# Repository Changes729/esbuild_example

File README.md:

# esbuild_example

## Chinese Users

``` sh
# install cnpm
npm install cnpm -g  --registry=https://registry.npm.taobao.org

cnpm install --save-dev @electron-forge/cli
cnpm exec --package=@electron-forge/cli -c "electron-forge import"
```

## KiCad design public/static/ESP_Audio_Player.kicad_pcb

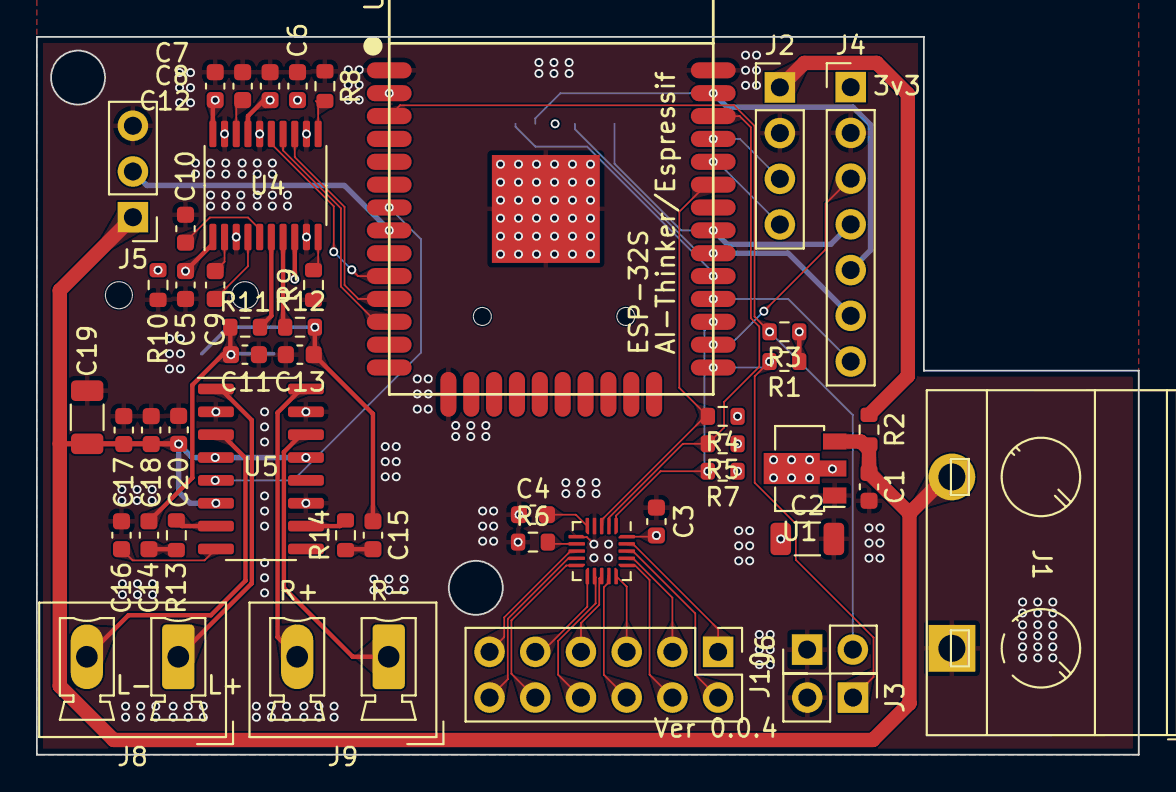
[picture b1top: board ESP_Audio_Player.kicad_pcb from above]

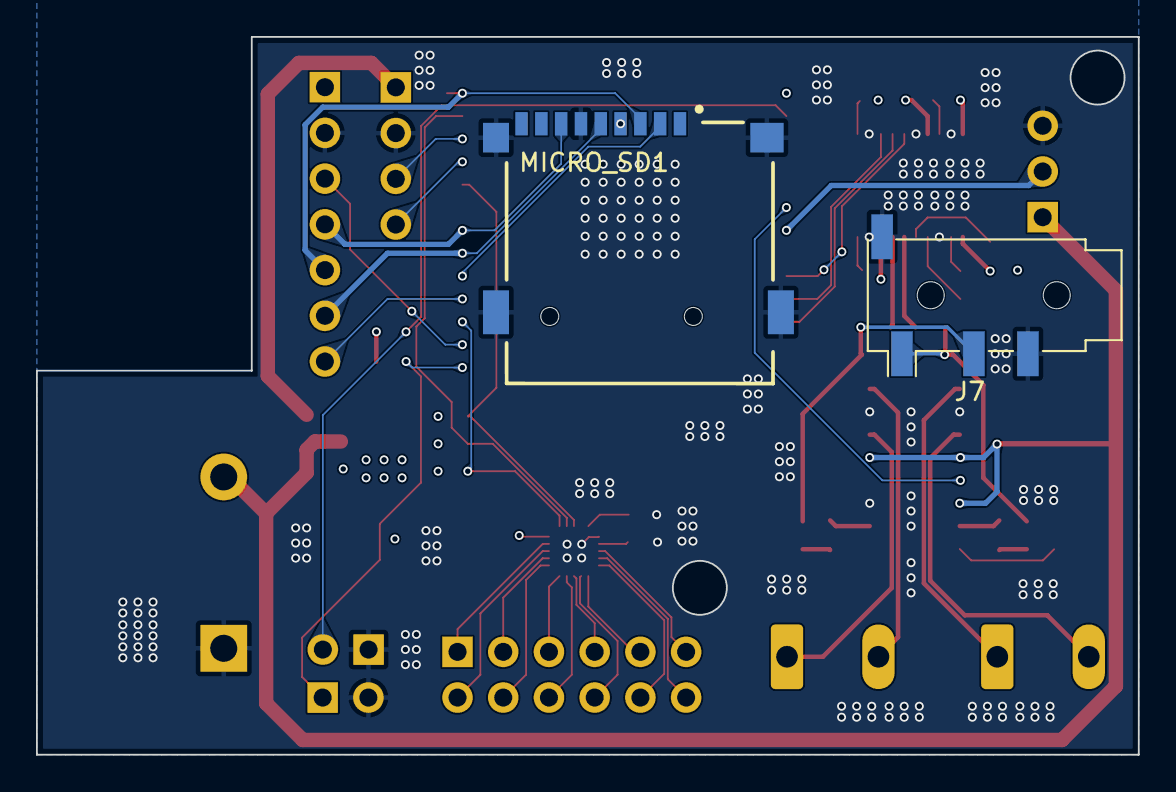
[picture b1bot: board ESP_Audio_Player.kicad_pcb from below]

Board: 4 copper layers, 61.2 x 39.9 mm, 50 parts (2 on the bottom side), 55 nets.

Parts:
C1, C8: 10uF; C_0603_1608Metric
C2: 10uF; C_1206_3216Metric
C3, C4, C5, C6, C7, C12, C14, C15, C16: 0.1uF; C_0603_1608Metric
C9, C10, C11, C13: 2.2uF; C_0603_1608Metric
C17, C18, C20: 1uF; C_0603_1608Metric
C19: 470uF; C_1206_3216Metric
J1: AC_IN; HB-9500
J2: UART_DOWNLOAD; PinHeader_1x04_P2.54mm_Vertical
J3: DMODE; PinHeader_1x02_P2.54mm_Vertical
J4: RC522_pins; PinHeader_1x07_P2.54mm_Vertical
J5: Conn_01x03; PinHeader_1x03_P2.54mm_Vertical
J6: Conn_01x02; PinHeader_1x02_P2.54mm_Vertical
J7: AudioJack4; Jack_3.5mm_PJ320D_Horizontal
J8, J9: Conn_01x02; PhoenixContact_MCV_1,5_2-G-5.08_1x02_P5.08mm_Vertical
J10: Conn_02x06_Odd_Even; PinHeader_2x06_P2.54mm_Vertical
MICRO_SD1: TF-01A
R1, R3: 12k; R_0603_1608Metric
R2: 0; R_0603_1608Metric
R4, R5, R7: 1k; R_0603_1608Metric
R6: 75k 1%; R_0603_1608Metric
R8, R9, R10: 100k; R_0603_1608Metric
R11, R12: 470; R_0603_1608Metric
R13, R14: 10k; R_0603_1608Metric
U1: AMS1117-3.3; SOT-89-3
U2: ESP-32S
U3: MPR121QR2; UQFN-20_3x3mm_P0.4mm
U4: PCM5102; TSSOP-20_4.4x6.5mm_P0.65mm
U5: PAM8403D; SOP-16_3.9x9.9mm_P1.27mm

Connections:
+3V3: C2.1, C3.1, C5.1, C6.1, C7.1, C8.1, J4.1, MICRO_SD1.4 (VDD), R1.1, R3.1, R4.1, R5.1, R7.1, R10.2, U1.2 (VO), U2.2 (3V3), U3.20 (VDD), U4.1 (CPVDD), U4.8 (AVDD), U4.17 (XSMT), U4.20 (DVDD)
+5V: C1.1, C17.2, C18.2, C19.2, C20.2, J1.2, J5.1, R2.2, U1.3 (VI), U5.4 (PVDD), U5.6 (VDD), U5.13 (PVDD)
/AUDIO_L: C11.2, C14.1, J7.T, R11.2
/AUDIO_MUTE: U2.7 (IO35), U5.5 (~MUTE)
/AUDIO_R: C13.2, C15.1, J7.R1, R12.2
/ESP_EN: J6.2, R3.2, U2.3 (EN)
/I2C_SCL: R5.2, U2.36 (IO22), U3.2 (SCL)
/I2C_SDA: R4.2, U2.33 (IO21), U3.3 (SDA)
/I2S_BCLK: U2.11 (IO26), U4.13 (BCK)
/I2S_DO: U2.12 (IO27), U4.14 (DIN)
/I2S_LRC: U2.10 (IO25), U4.15 (LRCK)
/IO0: J3.1, R1.2, U2.25 (IO0)
/MPR121/ELE0: J10.11, U3.8 (ELE0)
/MPR121/ELE1: J10.12, U3.9 (ELE1)
/MPR121/ELE2: J10.10, U3.10 (ELE2)
/MPR121/ELE3: J10.9, U3.11 (ELE3)
/MPR121/ELE4: J10.8, U3.12 (LED0/ELE4)
/MPR121/ELE5: J10.7, U3.13 (LED1/ELE5)
/MPR121/ELE6: J10.6, U3.14 (LED2/ELE6)
/MPR121/ELE7: J10.5, U3.15 (LED3/ELE7)
/MPR121/ELE8: J10.4, U3.16 (LED4/ELE8)
/MPR121/ELE9: J10.3, U3.17 (LED5/ELE9)
/MPR121/ELE10: J10.2, U3.18 (LED6/ELE10)
/MPR121/ELE11: J10.1, U3.19 (LED7/ELE11)
/PAM8403/+AOUT_L: J8.1, U5.1 (LOUT+)
/PAM8403/+AOUT_R: J9.2, U5.16 (ROUT+)
/PAM8403/-AOUT_L: J8.2, U5.3 (LOUT-)
/PAM8403/-AOUT_R: J9.1, U5.14 (ROUT-)
/PCM5102/DEMP_EN: R9.2, U4.10 (DEMP)
/PCM5102/FLT_EN: R8.2, U4.11 (FLT)
/RC522_SPI_CS: J4.7, U2.28 (IO17)
/RXD: J2.4, U2.34 (RXD0)
/SD_SPI_CS: MICRO_SD1.2 (CD/DAT3), U2.29 (IO5)
/TXD: J2.3, U2.35 (TXD0)
/VSPI_MISO: J4.4, MICRO_SD1.7 (DAT0), U2.31 (IO19)
/VSPI_MOSI: J4.5, MICRO_SD1.3 (CMD), U2.37 (IO23)
/VSPI_SCLK: J4.6, MICRO_SD1.5 (CLK), U2.30 (IO18)
/WS2812_SIG: J5.2, U2.8 (IO32)
/~IRQ: R7.2, U2.27 (IO16), U3.1 (~IRQ)
/~RC522_RST: J4.3, U2.26 (IO4)
GND: C1.2, C2.2, C3.2, C4.1, C5.2, C6.2, C7.2, C8.2, C10.1, C11.1, C12.1, C13.1, C16.1, C17.1, C18.1, C19.1, C20.1, J1.1, J2.2, J3.2, J4.2, J5.3, J6.1, J7.R2, J7.S, MICRO_SD1.6 (VSS), MICRO_SD1.MP1 (SHIELD), MICRO_SD1.MP2 (SHIELD), MICRO_SD1.MP3 (SHIELD), MICRO_SD1.MP4 (SHIELD), R6.1, R8.1, R9.1, R10.1, U1.1 (GND), U2.1 (GND), U2.15 (GND), U2.38 (GND), U2.39 (GND-PAD), U3.4 (ADDR), U3.6 (VSS), U4.3 (CPGND), U4.9 (AGND), U4.12 (SCK), U4.16 (FMT), U4.19 (DGND), U5.2 (PGND), U5.11 (GND), U5.15 (PGND)
unnamed: C14.2, R13.1
unnamed: C15.2, R14.1
unnamed: R6.2, U3.7 (REXT)
unnamed: C4.2, U3.5 (VREG)
unnamed: C9.1, U4.4 (CAPM)
unnamed: C9.2, U4.2 (CAPP)
unnamed: C12.2, U4.18 (LDOO)
unnamed: R11.1, U4.6 (OUTL)
unnamed: R12.1, U4.7 (OUTR)
unnamed: C10.2, U4.5 (VNEG)
unnamed: R13.2, U5.7 (INL)
unnamed: R14.2, U5.10 (INR)
unnamed: C16.2, U5.8 (VREF)
VDD: J2.1, R2.1

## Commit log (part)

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2024-02-23 [INTERNAL] 修改 esbuild 脚本，添加最小demo
2024-02-23 [INTERNAL] add electron support
2024-02-23 [INTERNAL] 修正
2024-03-01 添加 kicanvas 案例
2024-03-01 [INTERNAL] add pdf load example
2024-03-01 更新 html 版本和 react 动态版本的
2024-03-04 更新编译脚本。
2024-03-04 ThreeJS box example.
2024-03-22 添加 gltf example
2024-04-24 Wed Apr 24 10:22:11 CST 2024
2024-06-23 [NBF] test svg load in js, and operation with it.
2024-07-17 add excalidraw example.
2024-12-18 [INTERNAL] basic router usage.
2024-12-18 [INTERNAL] support router
2024-12-18 [INTERNAL] support scss.
2024-12-18 [INTERNAL] mass commit.
2024-12-18 [INTERNAL] merge some useless files into one react.
2024-12-19 Thu Dec 19 15:33:06 CST 2024
2024-12-21 [RELEASE] basic framework
2024-12-21 [INTERNAL] add milkdown example.
2025-01-29 marked example.
2025-01-29 update ipc call
2025-01-31 fix markdown load error. remove useless console output.
2025-02-02 test getPosition
2025-02-05 add test for web filesystem API.
2025-04-24 simple ts project
2025-04-24 add p5 example.
2025-07-05 at Jul 5 11:03:08 AM CST 2025
2025-08-18 esbuild alias support.
2025-08-19 update hash route
2025-08-19 use esbuild-plugin-alias.
2025-08-19 update router. add store. update sass.
2026-02-13 support prosemirror
2026-03-01 add html title
2026-05-31 update ts framework
